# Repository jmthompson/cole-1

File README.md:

COLE-1+
=======

This repository contains the schematics, board layouts, GAL code, and firmware
for the COLE-1 and COLE-1+ single-board computers.

The current HEAD of htis repository represents COLE-1+. To retrieve the files
for the older COLE-1, check out the v1.0 tag.

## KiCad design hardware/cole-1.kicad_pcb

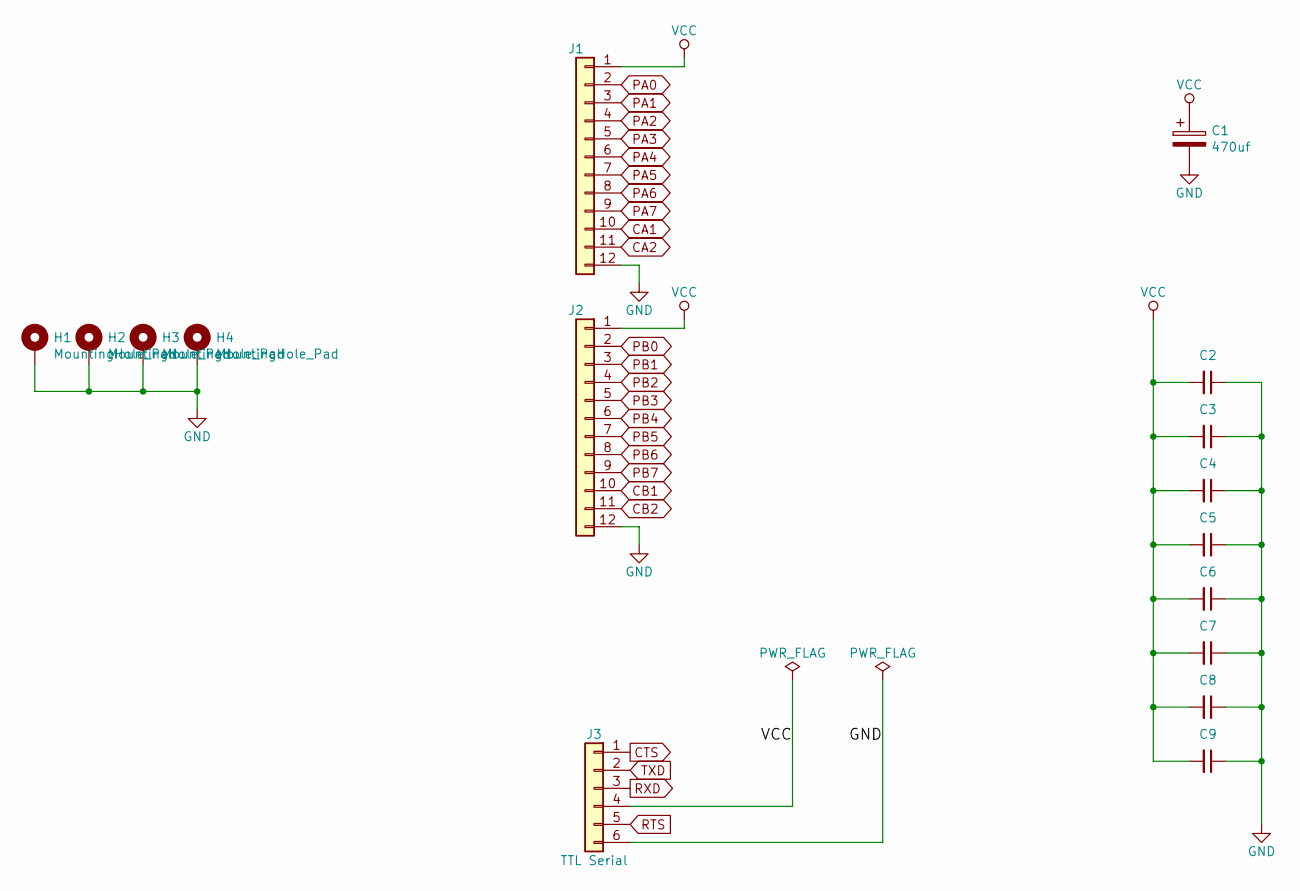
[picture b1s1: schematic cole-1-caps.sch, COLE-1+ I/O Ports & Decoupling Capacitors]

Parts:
C1: 470uf; CP_Radial_D13.0mm_P7.50mm
C2, C3, C4, C5, C6, C7, C8, C9: 0.1u; C_0805_2012Metric_Pad1.15x1.40mm_HandSolder
H1, H2, H3, H4: MountingHole_Pad; MountingHole_2.5mm_Pad_Via
J1: PORT A; PinHeader_1x12_P2.54mm_Vertical
J2: PORT B; PinHeader_1x12_P2.54mm_Vertical
J3: TTL Serial; PinHeader_1x06_P2.54mm_Vertical

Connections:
CA1: J1.10; also elsewhere on the board
CA2: J1.11; also elsewhere on the board
CB1: J2.10; also elsewhere on the board
CB2: J2.11; also elsewhere on the board
CTS: J3.1; also elsewhere on the board
GND: C1.2, C2.1, C3.1, C4.1, C5.1, C6.1, C7.1, C8.1, C9.1, H1.1, H2.1, H3.1, H4.1, J1.12, J2.12, J3.6; also elsewhere on the board
PA0: J1.2; also elsewhere on the board
PA1: J1.3; also elsewhere on the board
PA2: J1.4; also elsewhere on the board
PA3: J1.5; also elsewhere on the board
PA4: J1.6; also elsewhere on the board
PA5: J1.7; also elsewhere on the board
PA6: J1.8; also elsewhere on the board
PA7: J1.9; also elsewhere on the board
PB0: J2.2; also elsewhere on the board
PB1: J2.3; also elsewhere on the board
PB2: J2.4; also elsewhere on the board
PB3: J2.5; also elsewhere on the board
PB4: J2.6; also elsewhere on the board
PB5: J2.7; also elsewhere on the board
PB6: J2.8; also elsewhere on the board
PB7: J2.9; also elsewhere on the board
RTS: J3.5; also elsewhere on the board
RXD: J3.3; also elsewhere on the board
TXD: J3.2; also elsewhere on the board
VCC: C1.1, C2.2, C3.2, C4.2, C5.2, C6.2, C7.2, C8.2, C9.2, J1.1, J2.1, J3.4; also elsewhere on the board

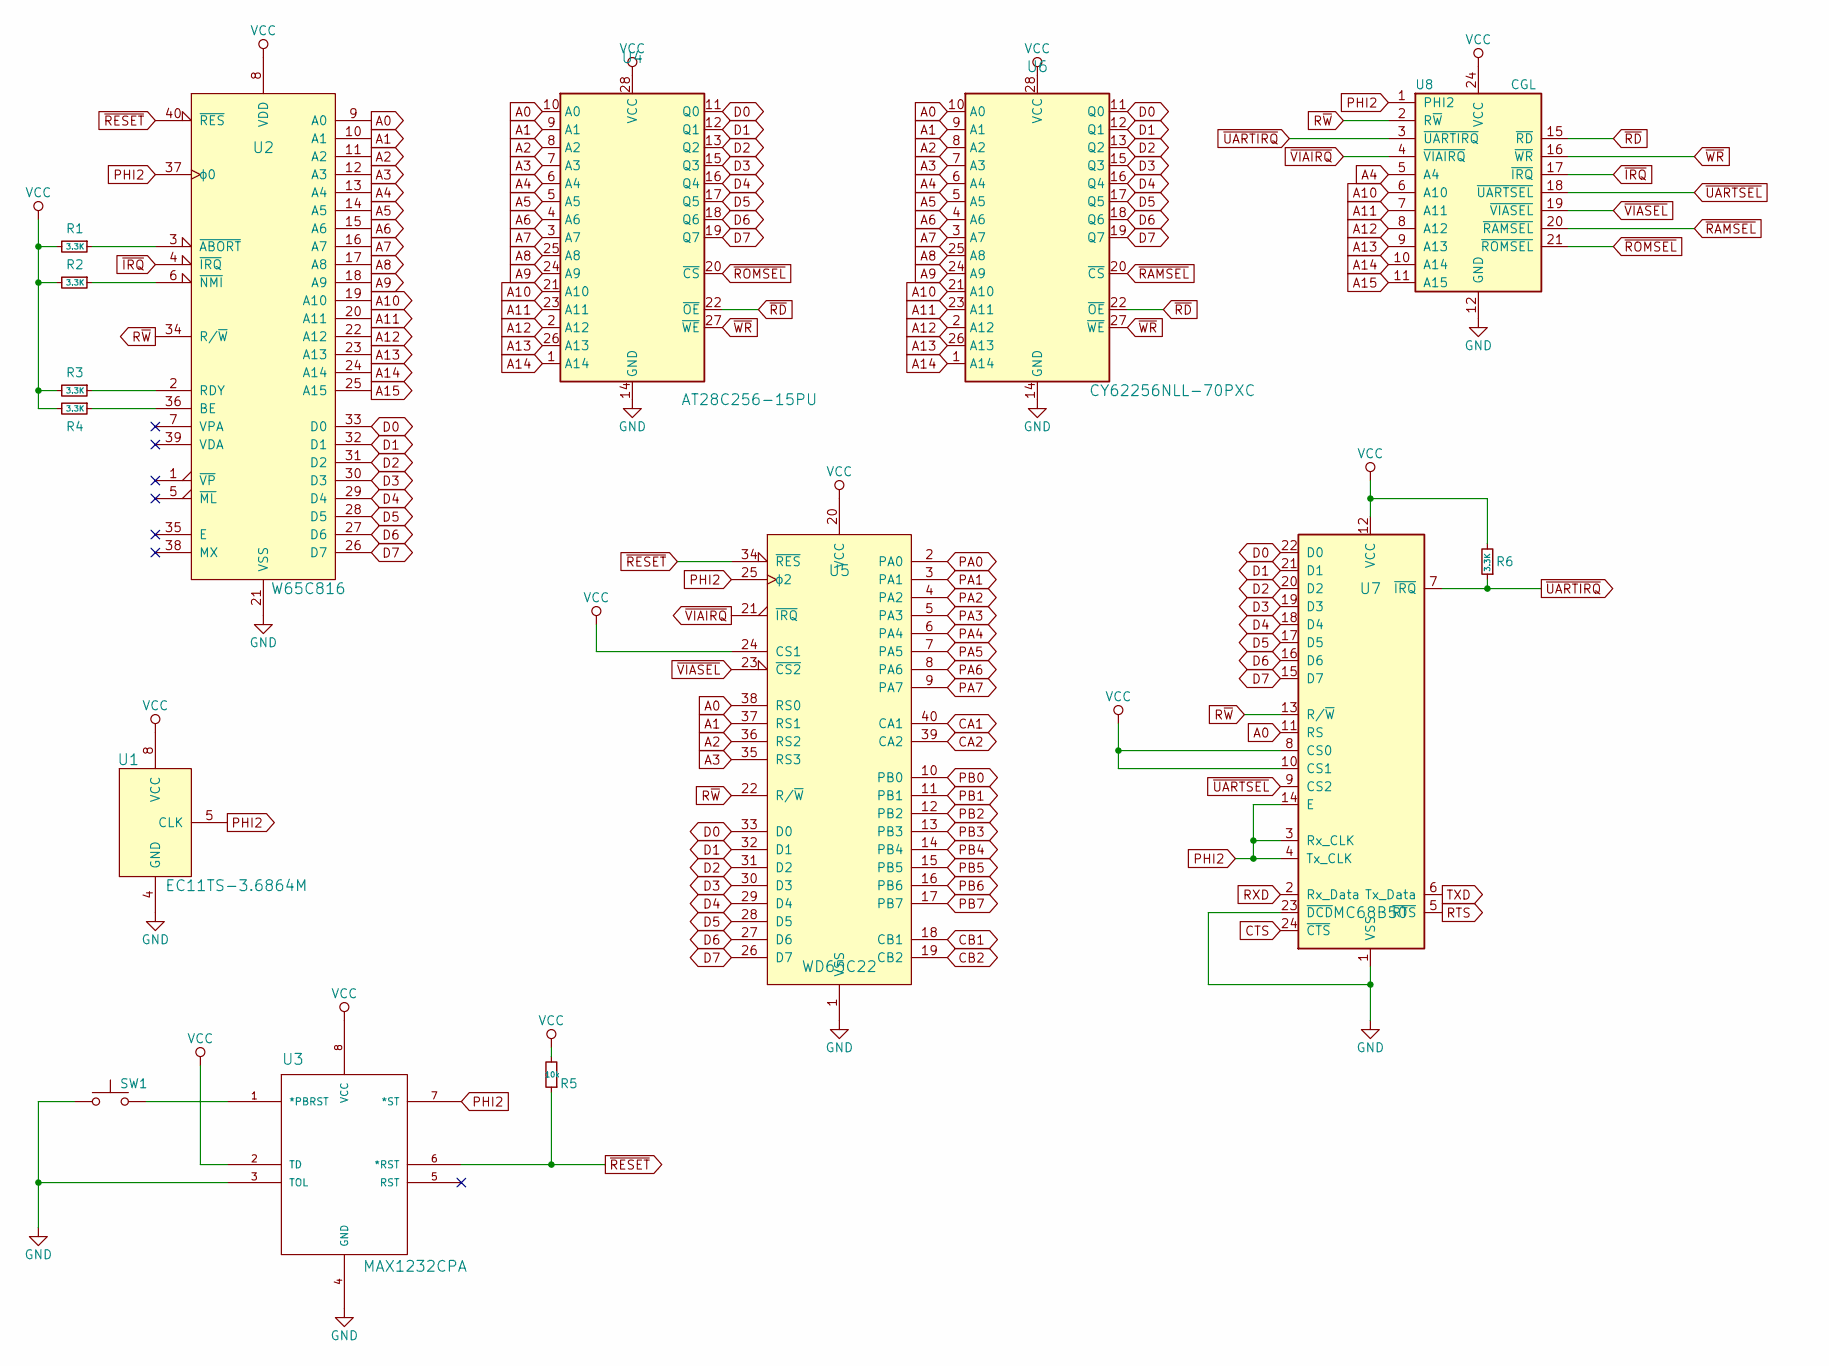
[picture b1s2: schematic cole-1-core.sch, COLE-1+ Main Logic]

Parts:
R1, R2, R3, R4, R6: 3.3K; R_0805_2012Metric_Pad1.15x1.40mm_HandSolder
R5: 10k; R_0805_2012Metric_Pad1.15x1.40mm_HandSolder
SW1: SW_Push; SW_PUSH_6mm_H5mm
U1: EC11TS-3.6864M; DIP-8_W7.62mm_Socket
U2: W65C816; DIP-40_W15.24mm_Socket
U3: MAX1232CPA; DIP-8_W7.62mm_Socket
U4: AT28C256-15PU; DIP-28_W15.24mm_Socket
U5: WD65C22; DIP-40_W15.24mm_Socket
U6: CY62256NLL-70PXC; DIP-28_W15.24mm_Socket
U7: MC68B50; DIP-24_W15.24mm_Socket
U8: CGL; DIP-24_W7.62mm_Socket

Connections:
A0: U2.9 (A0), U4.10 (A0), U5.38 (RS0), U6.10 (A0), U7.11 (RS)
A1: U2.10 (A1), U4.9 (A1), U5.37 (RS1), U6.9 (A1)
A2: U2.11 (A2), U4.8 (A2), U5.36 (RS2), U6.8 (A2)
A3: U2.12 (A3), U4.7 (A3), U5.35 (RS3), U6.7 (A3)
A4: U2.13 (A4), U4.6 (A4), U6.6 (A4), U8.5 (A4)
A5: U2.14 (A5), U4.5 (A5), U6.5 (A5)
A6: U2.15 (A6), U4.4 (A6), U6.4 (A6)
A7: U2.16 (A7), U4.3 (A7), U6.3 (A7)
A8: U2.17 (A8), U4.25 (A8), U6.25 (A8)
A9: U2.18 (A9), U4.24 (A9), U6.24 (A9)
A10: U2.19 (A10), U4.21 (A10), U6.21 (A10), U8.6 (A10)
A11: U2.20 (A11), U4.23 (A11), U6.23 (A11), U8.7 (A11)
A12: U2.22 (A12), U4.2 (A12), U6.2 (A12), U8.8 (A12)
A13: U2.23 (A13), U4.26 (A13), U6.26 (A13), U8.9 (A13)
A14: U2.24 (A14), U4.1 (A14), U6.1 (A14), U8.10 (A14)
A15: U2.25 (A15), U8.11 (A15)
CA1: U5.40 (CA1); also elsewhere on the board
CA2: U5.39 (CA2); also elsewhere on the board
CB1: U5.18 (CB1); also elsewhere on the board
CB2: U5.19 (CB2); also elsewhere on the board
CTS: U7.24 (~CTS); also elsewhere on the board
D0: U2.33 (D0), U4.11 (Q0), U5.33 (D0), U6.11 (Q0), U7.22 (D0)
D1: U2.32 (D1), U4.12 (Q1), U5.32 (D1), U6.12 (Q1), U7.21 (D1)
D2: U2.31 (D2), U4.13 (Q2), U5.31 (D2), U6.13 (Q2), U7.20 (D2)
D3: U2.30 (D3), U4.15 (Q3), U5.30 (D3), U6.15 (Q3), U7.19 (D3)
D4: U2.29 (D4), U4.16 (Q4), U5.29 (D4), U6.16 (Q4), U7.18 (D4)
D5: U2.28 (D5), U4.17 (Q5), U5.28 (D5), U6.17 (Q5), U7.17 (D5)
D6: U2.27 (D6), U4.18 (Q6), U5.27 (D6), U6.18 (Q6), U7.16 (D6)
D7: U2.26 (D7), U4.19 (Q7), U5.26 (D7), U6.19 (Q7), U7.15 (D7)
GND: SW1.1, U1.4 (GND), U2.21 (VSS), U3.3 (TOL), U3.4 (GND), U4.14 (GND), U5.1 (VSS), U6.14 (GND), U7.1 (VSS), U7.23 (~DCD), U8.12 (GND); also elsewhere on the board
unnamed: R1.1, U2.3 (~ABORT)
unnamed: R2.1, U2.6 (~NMI)
unnamed: R3.1, U2.2 (RDY)
unnamed: R4.1, U2.36 (BE)
unnamed: SW1.2, U3.1 (*PBRST)
PA0: U5.2 (PA0); also elsewhere on the board
PA1: U5.3 (PA1); also elsewhere on the board
PA2: U5.4 (PA2); also elsewhere on the board
PA3: U5.5 (PA3); also elsewhere on the board
PA4: U5.6 (PA4); also elsewhere on the board
PA5: U5.7 (PA5); also elsewhere on the board
PA6: U5.8 (PA6); also elsewhere on the board
PA7: U5.9 (PA7); also elsewhere on the board
PB0: U5.10 (PB0); also elsewhere on the board
PB1: U5.11 (PB1); also elsewhere on the board
PB2: U5.12 (PB2); also elsewhere on the board
PB3: U5.13 (PB3); also elsewhere on the board
PB4: U5.14 (PB4); also elsewhere on the board
PB5: U5.15 (PB5); also elsewhere on the board
PB6: U5.16 (PB6); also elsewhere on the board
PB7: U5.17 (PB7); also elsewhere on the board
PHI2: U1.5 (CLK), U2.37 (ϕ0), U3.7 (*ST), U5.25 (ϕ2), U7.3 (Rx_CLK), U7.4 (Tx_CLK), U7.14 (E), U8.1 (PHI2)
RTS: U7.5 (~RTS); also elsewhere on the board
RXD: U7.2 (Rx_Data); also elsewhere on the board
R~W: U2.34 (R/~W), U5.22 (R/~W), U7.13 (R/~W), U8.2 (R~W)
TXD: U7.6 (Tx_Data); also elsewhere on the board
VCC: R1.2, R2.2, R3.2, R4.2, R5.2, R6.2, U1.8 (VCC), U2.8 (VDD), U3.2 (TD), U3.8 (VCC), U4.28 (VCC), U5.20 (VCC), U5.24 (CS1), U6.28 (VCC), U7.8 (CS0), U7.10 (CS1), U7.12 (VCC), U8.24 (VCC); also elsewhere on the board
~IRQ: U2.4 (~IRQ), U8.17 (~IRQ)
~RAMSEL: U6.20 (~CS), U8.20 (~RAMSEL)
~RD: U4.22 (~OE), U6.22 (~OE), U8.15 (~RD)
~RESET: R5.1, U2.40 (~RES), U3.6 (*RST), U5.34 (~RES)
~ROMSEL: U4.20 (~CS), U8.21 (~ROMSEL)
~UARTIRQ: R6.1, U7.7 (~IRQ), U8.3 (~UARTIRQ)
~UARTSEL: U7.9 (CS2), U8.18 (~UARTSEL)
~VIAIRQ: U5.21 (~IRQ), U8.4 (~VIAIRQ)
~VIASEL: U5.23 (~CS2), U8.19 (~VIASEL)
~WR: U4.27 (~WE), U6.27 (~WE), U8.16 (~WR)

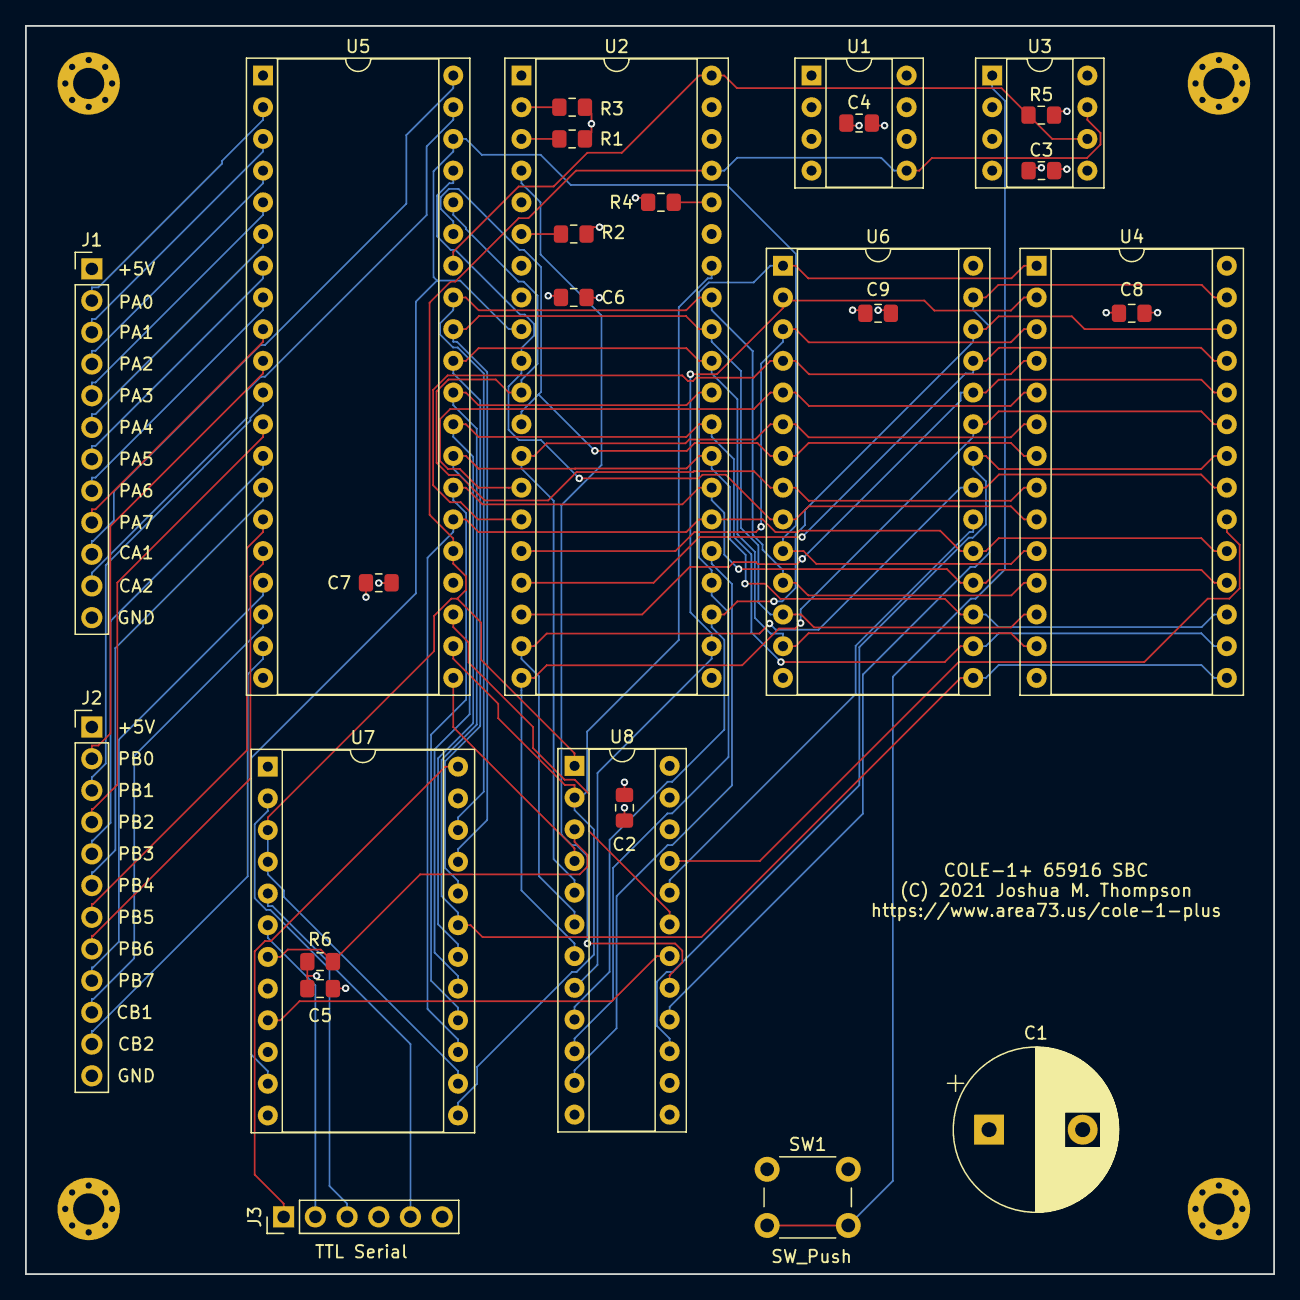
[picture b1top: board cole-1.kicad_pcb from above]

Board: 4 copper layers, 100.0 x 100.0 mm, 31 parts (0 on the bottom side), 67 nets.

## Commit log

2018-01-04 Add missing "#"s to constant references Add a delay to serial_write to allow for previous char to transmit before giving up and erroring out.
2018-01-04 Move the LED flash back to the right spot
2018-01-04 Split fw.s into osentry.s and vectors.s, and rame ld65 config file from fw.cfg to cole-1.cfg.
2018-01-08 Added a monitor program now, currently only handles BRKs and memory dump commands Added support for the console to not be serial, by having all ROM code do its I/O via the new console_read an console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
2018-01-08 - Change WE on the EEPROM to be tied to ground, like it is on the breadboard prototype. - Change TD pin on the MAX1232 to bre tied to Vcc, which raises the watchdog timeout to 1.2s. - Add Vcc and GND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
2018-01-13 change VIA port connectors to 2x12 connectors with per-signal ground wires
2018-01-13 switch to a DIP-8 oscillator, and fix footprint for MAX1232
2018-01-14 Final schematic and PCB layout.
2018-01-14 - document the memory map (finally!) - monitor now has working memory dump and run commands - removed watchdog code since it's now hard-wired to Phi2 - initial skeletal implementation of SPI on VIA p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
2018-01-14 Change this from a function address table to a jump table.
2018-01-14 - Add a generated version.s file that defines a rom_version symbol containing the current ROM version as a date string - Change boot banner display to use the rom_version string instead of the hard-c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
2018-01-14 This is the first of many patches to clean up and organize the EhBASIC code. The bulk of this patch is tab=>space conversion and reformatting, with a few minor tweaks:
    1. Removed Memory size prompt and just use Ram_top always.
    2. Removed the Ready prompt
    3. Added an AppleSoft-style "]" input prompt
    4. At boot time, display the boot banner and then the memory size immediately after
    5. Update LAB_SYS to accomodate the OSVECTOR area becoming a jump table.
2018-01-15 add XModem-CRC send/receive code, and add 'r' monitor command to accept xmodem uploads to a location in memory
2018-01-15 - remove code from XModemSend that puts the start address in the first two bytes of block 0 - updated monitor to use '<' for xmodem receive, and '>' for xmodem send - added disassembler and associate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
2018-06-02 fix footprint for the ACIA
2018-06-02 Change to clk/64 for ACIA to match change in hw design
2018-06-02 Update PHI2 to reflect final hardare at 4 MHz, change SPI device select devices via 74HC138, and add bug fixes to make SPI functional
2018-06-02 Misc bug fixes in writeln, optimized print_hex_digit, and added initial JEROS hook.
2018-06-02 Reorganize source files into subdirectories by module.
2018-06-02 Consolidate all of the firmware data usage into a single "DATA" segment from $0200-$07FF. Also separate the firmware data and user data into separate memory areas, and change the EhBasic code to use 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
2019-03-04 Final commit
2021-08-10 Updated schematics, board layout, and GAL code for COLE-1+
2021-08-12 Add A10 and A11 routing to GAL, and update GAL equations
2021-08-19 Replace firmware with modified COLE-2 firmware
2021-08-20 Update memory_map.txt to reflect new RAM layout Change monitor run command from "r" to "g" to match Apple II monitor Add code to disassembler to track M/X flags
2021-08-22 Memory map layout change: LOWROM is now BOOTROM at $F000; HIGHROM is now BIOSROM at $9000.
    Reduced ROM size by 2k so that a copy of it can fit entirely in the user RAM area.
    Added a utility for flashing the ROM via Xmodem upload
2021-08-22 Cleanup; move docs to folder, remove unused files
2021-08-22 Move all bios direct page variables to a single file for easier management
2021-08-22 Remove set_kernel_dp macro; COP dispatcher now automatically sets the BIOS DP on syscall entry.

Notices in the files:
hardware/cole-1.kicad_pcb:
(C) 2021 Joshua M. Thompson
